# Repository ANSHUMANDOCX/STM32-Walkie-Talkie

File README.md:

# STM32 LoRa Walkie-Talkie

A custom walkie-talkie built on a bare STM32F411RET6 microcontroller and SX1278 LoRa radio module, designed from scratch in KiCad with a fully custom PCB.

---
## Inspiration
I made this STM32 Walkie Talkie to learn about STM32 since i have never worked with The ST chips and LoRa hence i though of it as a good opportunity for me to learn about these and make a good project out of it too. Also it gives me a chance to perfect wireless radio skills.
## Hardware 

| Component | Part | Purpose |
|---|---|---|
| MCU | STM32F411RET6 (LQFP-64) | Main processor |
| LoRa radio | Ra-02 (SX1278, 433 MHz) | Wireless communication |
| Mic amp | MAX9814 | Electret microphone amplifier with AGC |
| Speaker amp | MAX98357A | I2S class-D speaker amplifier |
| Display | Nokia 5110 (PCD8544) | Status display |
| LDO | MIC5219-3.3 | 3.3V regulation |
| Charger | TP4056 | Li-Ion battery charging |
| Protection | DW01A + AO3401A + FS8205 | Battery over/under voltage protection and Load sharing |
| Battery | 18650 Li-Ion (2500mAh) | Power source |

---

## Features

- Push-to-talk (PTT) voice transmission over LoRa
- Nokia 5110 display showing TX/RX status, RSSI, battery %, charging state
- LED indicators for TX and RX
- PWM buzzer with distinct tones for PTT, incoming call, low battery, charging complete etc
- Battery percentage via voltage divider on ADC
- Load sharing circuit — runs on USB power while charging battery
- TP4056 charging status readable by firmware
- SWD debug header for ST-Link V2 programming
- When USB is connected the system runs off USB directly and the battery charges independently. When USB is removed the load sharing circuit seamlessly switches to battery power.

---
Firmware us teseted and works fine
## Build 

Demo Links -
https://youtu.be/u5zcdfWUoc0?si=na0F3SUNMQuTFcsV
https://youtube.com/shorts/hGkoWbwqjJw?si=Fj_72HcpeDVytp3i
https://youtube.com/shorts/hm_hJY4Z-SY?si=CA80bZE5GAXgrqjr
https://youtu.be/_cB_pIMBPP0?si=Omx-B7MlO4rouQgG
https://youtu.be/SAzjPhdUsmI?si=3dBDZw_p-0JPJG1Q

## Schematic PCB and CAD

## BOM

| Product Name       | Part / Model         | Qty | Unit Price ($) | Total ($) | Vendor  | Link |
|-------------------|----------------------|-----|----------------|-----------|---------|------|
| 8MHz SMD Crystal  | X32258MOB4SI         | 2   | 0.08           | 0.15      | ROBU    | https://robu.in/product/x32258mob4si-yxc-crystal-oscillators-8mhz-surface-mount-crystal-12pf-%c2%b110ppm-%c2%b120ppm-smd3225-4p-crystals-rohs |
| STM32 MCU         | STM32F411RET6        | 2   | 2.88           | 5.76      | ROBU    | https://robu.in/product/stm32f411ret6-stmicroelectronics-3-6v-32-bit-risc-512kb-flash-arm-cortex-m4-mcu-dsp-fpu-art-accelerator-64-pin-lqfp |
| Push Button       | DS-316 SPST          | 2   | 0.12           | 0.24      | ROBU    | https://robu.in/product/ds-316-mini-push-button-switch-spst-2pinoff-on |
| IPEX to SMA Cable | RG178 15cm           | 2   | 1.60           | 3.20      | ROBU    | https://robu.in/product/15cm-ipex1-to-sma-female-connector-cable-11mm-rg178 |
| Mic Amplifier     | MAX9814ETDT          | 2   | 2.87           | 5.74      | ROBU    | https://robu.in/product/max9814etdt-analog-devices-microphone-amplifier-2-7-v-to-5-5-v-supply-1-ma-out-40-db-50db-60db-gain-tdfn-14 |
| Speaker AMP       | MAX98357A            | 2   | 2.37           | 4.73      | ROBU    | https://robu.in/product/1-month-warranty-560 |
| LoRa Module       | SX1278 RA-02         | 2   | 3.74           | 7.48      | ROBU    | https://robu.in/product/sx1278-lora-module-ra-02-433mhz-wireless-spread-spectrum-transmission |
| JST Connector     | 8-pin XH 2.54mm      | 2   | 0.77           | 1.55      | ROBU    | https://robu.in/product/8-pin-jst-xh-2-54mm-pitch-plug-and-socket-with-cable-3pcs |
| Speaker           | 8Ω Small Speaker     | 2   | 0.75           | 1.51      | Generic | https://sharvielectronics.com/product/speaker-8-ohm-trumpet-diameter-40mm-2-watt/ |
| Microphone        | Electret Mic Capsule | 2   | 0.11           | 0.22      | Generic | https://inkocean.in/products/microphones-9767-9-7-electret-microphone-a-microphone-with-pins-sensitivity-58 |
| Display           | Nokia 5110 LCD       | 2   | 3.01           | 6.02      | Generic | https://inkocean.in/products/nokia-5110-lcd-red-screen-blue-lcd-screen-module |
|HeatSet Insert Attatchment||1|6.2|6.2|Amazon|https://www.amazon.in/amiciTools-Heat-Insert-Soldering-Printing/dp/B0GFDZ5GL9/ref=asc_df_B0GFDZ5GL9?mcid=fe31e451fd45349b9016d36cd31d3876&hvadid=709875643605&hvpos=&hvnetw=g&hvrand=10961091970810594313&hvpone=&hvptwo=&hvqmt=&hvdev=c&hvdvcmdl=&hvlocint=&hvlocphy=1007828&hvtargid=pla-2466325763035&psc=1&hvocijid=10961091970810594313-B0GFDZ5GL9-&hvexpln=0|
| Passives          | SMD passives         | 1   | 5.38           | 5.38      | —       | — |
| PCB               | —                    | 1   | 3.00           | 3.00      | ALLPCB  | — |
| **TOTAL** |  |  |  | **44.98** |  |  |

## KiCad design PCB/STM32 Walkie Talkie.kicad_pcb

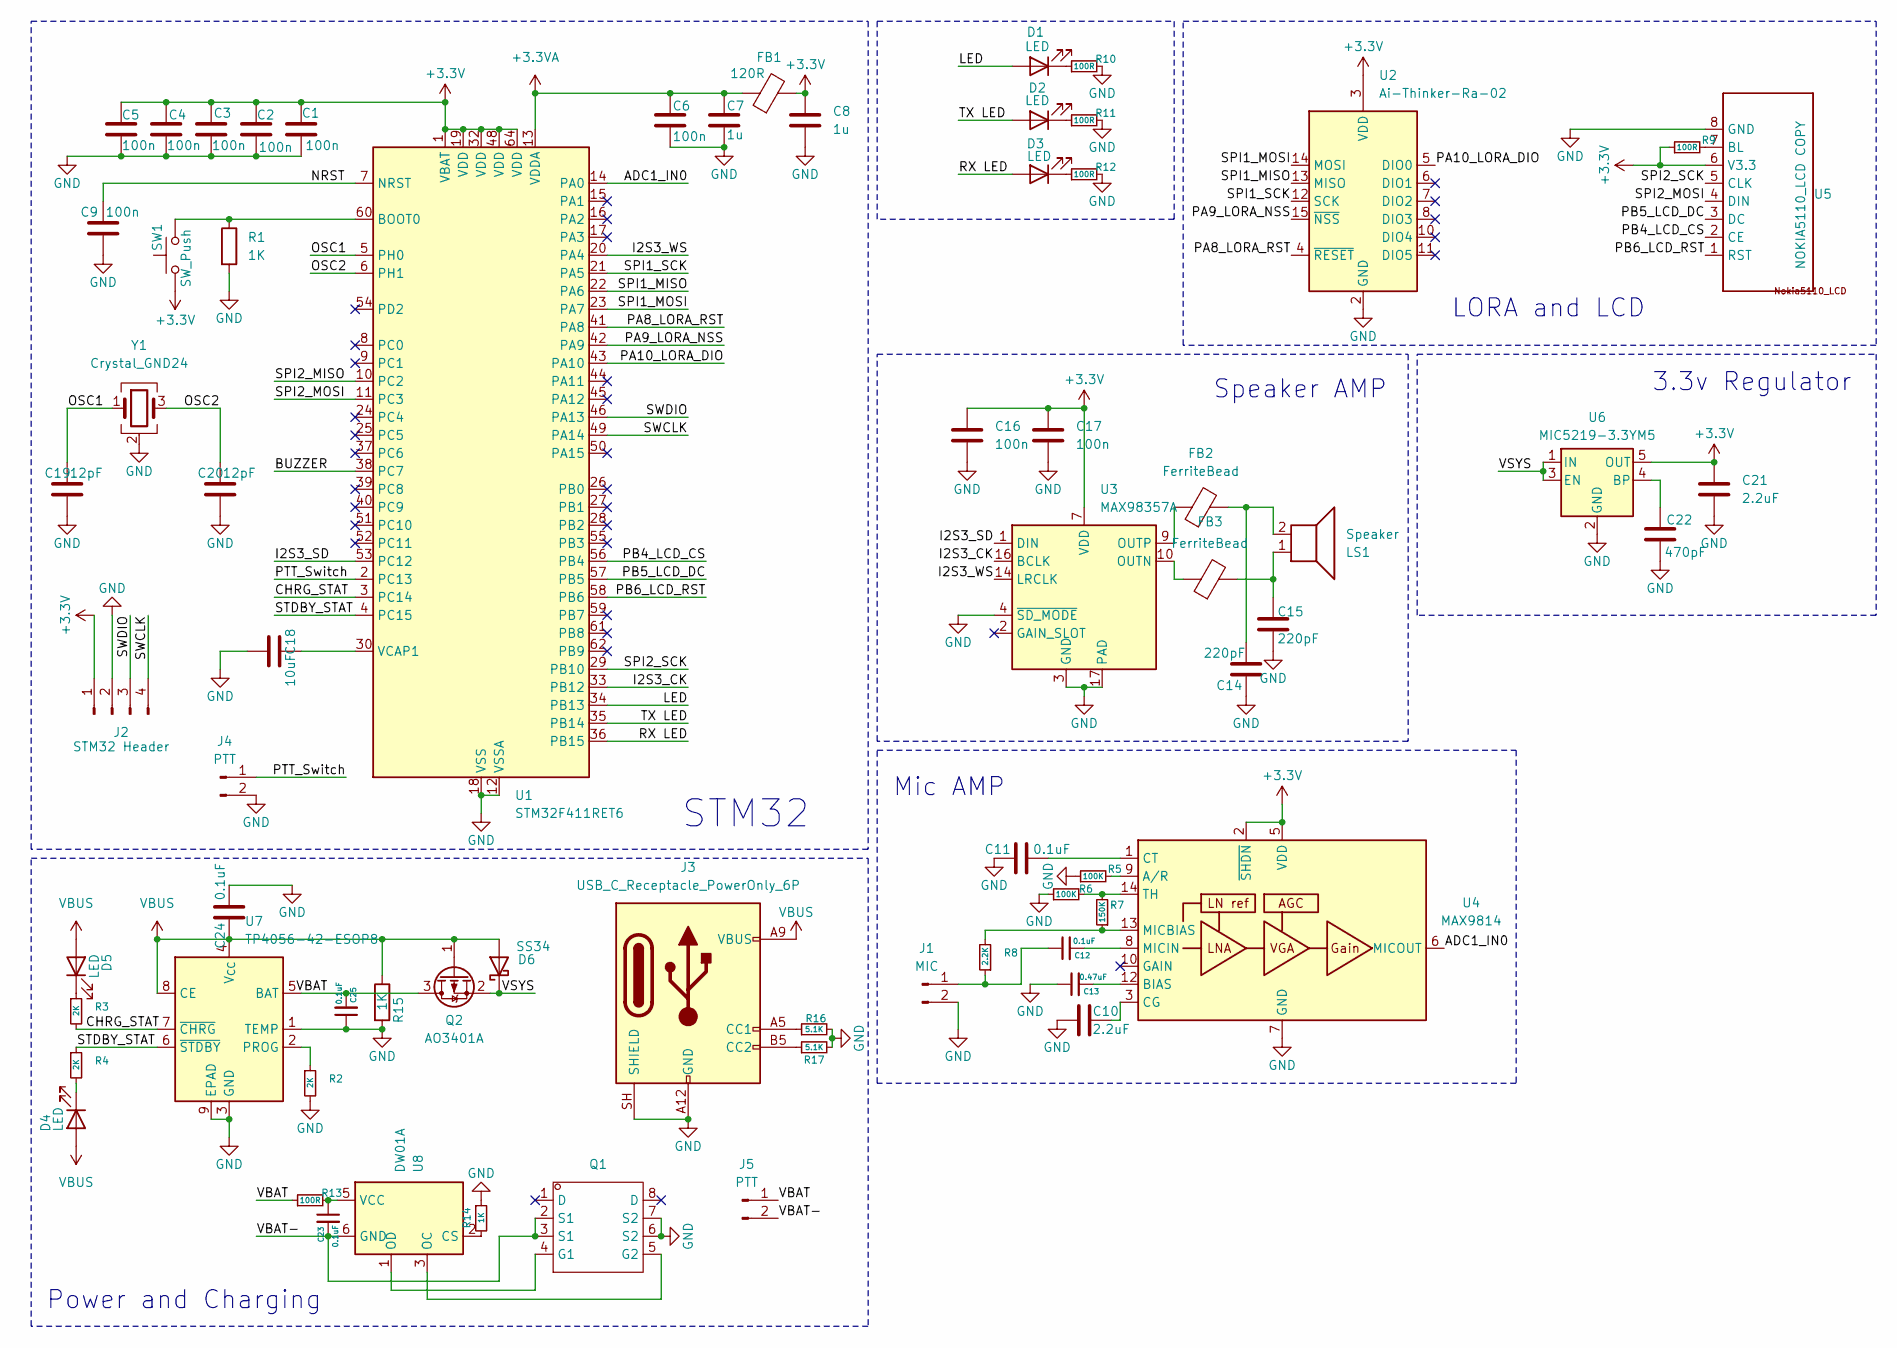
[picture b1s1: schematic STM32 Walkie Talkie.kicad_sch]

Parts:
C1, C2, C3, C4, C5, C6, C9, C16, C17: 100n; R_0603_1608Metric
C7, C8: 1u; R_0603_1608Metric
C10, C21: 2.2uF; C_0805_2012Metric
C11, C12, C23, C24, C25: 0.1uF; R_0603_1608Metric
C13: 0.47uF; R_0603_1608Metric
C14, C15: 220pF; R_0603_1608Metric
C18: 10uF; C_0805_2012Metric
C19, C20: 12pF; R_0603_1608Metric
C22: 470pF; R_0603_1608Metric
D1, D2, D3, D4, D5: LED; LED_0603_1608Metric
D6: SS34; D_SMA
FB1: 120R; R_0603_1608Metric
FB2, FB3: FerriteBead; R_0603_1608Metric
J1: MIC; JST_XH_B2B-XH-A_1x02_P2.50mm_Vertical
J2: STM32 Header; PinHeader_1x04_P2.54mm_Vertical
J3: USB_C_Receptacle_PowerOnly_6P; USB_C_Receptacle_GCT_USB4125-xx-x_6P_TopMnt_Horizontal
J4, J5: PTT; JST_XH_B2B-XH-A_1x02_P2.50mm_Vertical
LS1: Speaker; JST_XH_B2B-XH-A_1x02_P2.50mm_Vertical
Q1: TSSOP-8_L4.4-W3.0-P0.65-LS6.4-BL-2; Manufacturer Part FS8205A; LCSC Part Name 2个N沟道 耐压:20V 电流:6A
Q2: AO3401A; SOT-23
R1, R14, R15: 1K; R_0603_1608Metric
R2, R3, R4: 2K; R_0603_1608Metric
R5, R6: 100K; R_0603_1608Metric
R7: 150K; R_0603_1608Metric
R8: 2.2K; R_0603_1608Metric
R9, R10, R11, R12, R13: 100R; R_0603_1608Metric
R16, R17: 5.1K; R_0603_1608Metric
SW1: SW_Push; SW_SPST_TS-1088-xR025
U1: STM32F411RET6; LQFP-64_10x10mm_P0.5mm
U2: Ai-Thinker-Ra-02; Ai-Thinker-Ra-01-LoRa
U3: MAX98357A; TQFN-16-1EP_3x3mm_P0.5mm_EP1.23x1.23mm
U4: MAX9814; TDFN-14-1EP_3x3mm_P0.4mm_EP1.78x2.35mm
U5: NOKIA5110_LCD COPY; JST_XH_B8B-XH-A_1x08_P2.50mm_Vertical
U6: MIC5219-3.3YM5; SOT-23-5
U7: TP4056-42-ESOP8; SOIC-8-1EP_3.9x4.9mm_P1.27mm_EP2.41x3.3mm_ThermalVias
U8: DW01A; SOT-23-6
Y1: Crystal_GND24; Crystal_SMD_SeikoEpson_TSX3225-4Pin_3.2x2.5mm

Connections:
+3.3V: C1.1, C2.1, C3.1, C4.1, C5.1, C8.1, C16.1, C17.1, C21.1, FB1.2, J2.1, R9.1, SW1.1, U1.1 (VBAT), U1.19 (VDD), U1.32 (VDD), U1.48 (VDD), U1.64 (VDD), U2.3 (VDD), U3.7 (VDD), U3.8 (VDD), U4.2 (~SHDN), U4.5 (VDD), U5.6 (V3.3), U6.5 (OUT)
+3.3VA: C6.1, C7.1, FB1.1, U1.13 (VDDA)
/ADC1_IN0: U1.14 (PA0), U4.6 (MICOUT)
/BUZZER: U1.38 (PC7)
/CHRG_STAT: R3.2, U1.3 (PC14), U7.7 (~CHRG)
/I2S3_CK: U1.33 (PB12), U3.16 (BCLK)
/I2S3_SD: U1.53 (PC12), U3.1 (DIN)
/I2S3_WS: U1.20 (PA4), U3.14 (LRCLK)
/LED: D1.2 (A), U1.34 (PB13)
/NRST: C9.1, U1.7 (NRST)
/OSC1: C19.1, U1.5 (PH0), Y1.1
/OSC2: C20.1, U1.6 (PH1), Y1.3
/PA8_LORA_RST: U1.41 (PA8), U2.4 (~RESET)
/PA9_LORA_NSS: U1.42 (PA9), U2.15 (~NSS)
/PA10_LORA_DIO: U1.43 (PA10), U2.5 (DIO0)
/PB4_LCD_CS: U1.56 (PB4), U5.2 (CE)
/PB5_LCD_DC: U1.57 (PB5), U5.3 (DC)
/PB6_LCD_RST: U1.58 (PB6), U5.1 (RST)
/PTT_Switch: J4.1, U1.2 (PC13)
/RX LED: D3.2 (A), U1.36 (PB15)
/SPI1_MISO: U1.22 (PA6), U2.13 (MISO)
/SPI1_MOSI: U1.23 (PA7), U2.14 (MOSI)
/SPI1_SCK: U1.21 (PA5), U2.12 (SCK)
/SPI2_MISO: U1.10 (PC2)
/SPI2_MOSI: U1.11 (PC3), U5.4 (DIN)
/SPI2_SCK: U1.29 (PB10), U5.5 (CLK)
/STDBY_STAT: R4.1, U1.4 (PC15), U7.6 (~STDBY)
/SWCLK: J2.4, U1.49 (PA14)
/SWDIO: J2.3, U1.46 (PA13)
/TX LED: D2.2 (A), U1.35 (PB14)
/VBAT: C25.2, J5.1, Q2.3 (D), R13.1, U7.5 (BAT)
/VBAT-: C23.2, J5.2, Q1.2 (S1), Q1.3 (S1), U8.6 (GND)
/VSYS: D6.1 (K), Q2.2 (S), U6.1 (IN), U6.3 (EN)
GND: C1.2, C2.2, C3.2, C4.2, C5.2, C6.2, C7.2, C8.2, C9.2, C10.1, C11.1, C13.1, C14.2, C15.2, C16.2, C17.2, C18.2, C19.2, C20.2, C21.2, C22.2, C24.2, C25.1, J1.2, J2.2, J3.A12 (GND), J3.B12 (GND), J3.SH (SHIELD), J4.2, Q1.6 (S2), Q1.7 (S2), R1.2, R2.2, R5.1, R6.1, R10.2, R11.2, R12.2, R14.1, R15.2, R16.2, R17.2, U1.12 (VSSA), U1.18 (VSS), U1.31 (VSS), U1.47 (VSS), U1.63 (VSS), U2.1 (GND), U2.2 (GND), U2.9 (GND), U2.16 (GND), U3.3 (GND), U3.4 (~SD_MODE), U3.11 (GND), U3.15 (GND), U3.17 (PAD), U4.4 (GND), U4.7 (GND), U4.11 (GND), U4.15 (GND), U5.8 (GND), U6.2 (GND), U7.1 (TEMP), U7.3 (GND), U7.9 (EPAD), U8.4 (TD), Y1.2 (G), Y1.4 (G)
unnamed: C14.1, FB2.2, LS1.2
unnamed: C15.1, FB3.2, LS1.1
unnamed: D1.1 (K), R10.1
unnamed: D2.1 (K), R11.1
unnamed: D3.1 (K), R12.1
unnamed: D4.1 (K), R4.2
unnamed: D5.1 (K), R3.1
unnamed: C12.1, J1.1, R8.1
unnamed: J3.A5 (CC1), R16.1
unnamed: J3.B5 (CC2), R17.1
unnamed: Q1.4 (G1), U8.1 (OD)
unnamed: Q1.5 (G2), U8.3 (OC)
unnamed: R1.1, SW1.2, U1.60 (BOOT0)
unnamed: C18.1, U1.30 (VCAP1)
unnamed: FB3.1, U3.10 (OUTN)
unnamed: FB2.1, U3.9 (OUTP)
unnamed: R5.2, U4.9 (A/R)
unnamed: C13.2, U4.12 (BIAS)
unnamed: C10.2, U4.3 (CG)
unnamed: C11.2, U4.1 (CT)
unnamed: R7.1, R8.2, U4.13 (MICBIAS)
unnamed: C12.2, U4.8 (MICIN)
unnamed: R6.2, R7.2, U4.14 (TH)
unnamed: R9.2, U5.7 (BL)
unnamed: C22.1, U6.4 (BP)
unnamed: R2.1, U7.2 (PROG)
unnamed: R14.2, U8.2 (CS)
unnamed: C23.1, R13.2, U8.5 (VCC)
VBUS: C24.1, D4.2 (A), D5.2 (A), D6.2 (A), J3.A9 (VBUS), J3.B9 (VBUS), Q2.1 (G), R15.1, U7.4 (V_{CC}), U7.8 (CE)

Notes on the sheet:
3.3v Regulator
Mic AMP
Speaker AMP
Power and Charging
LORA and LCD
STM32

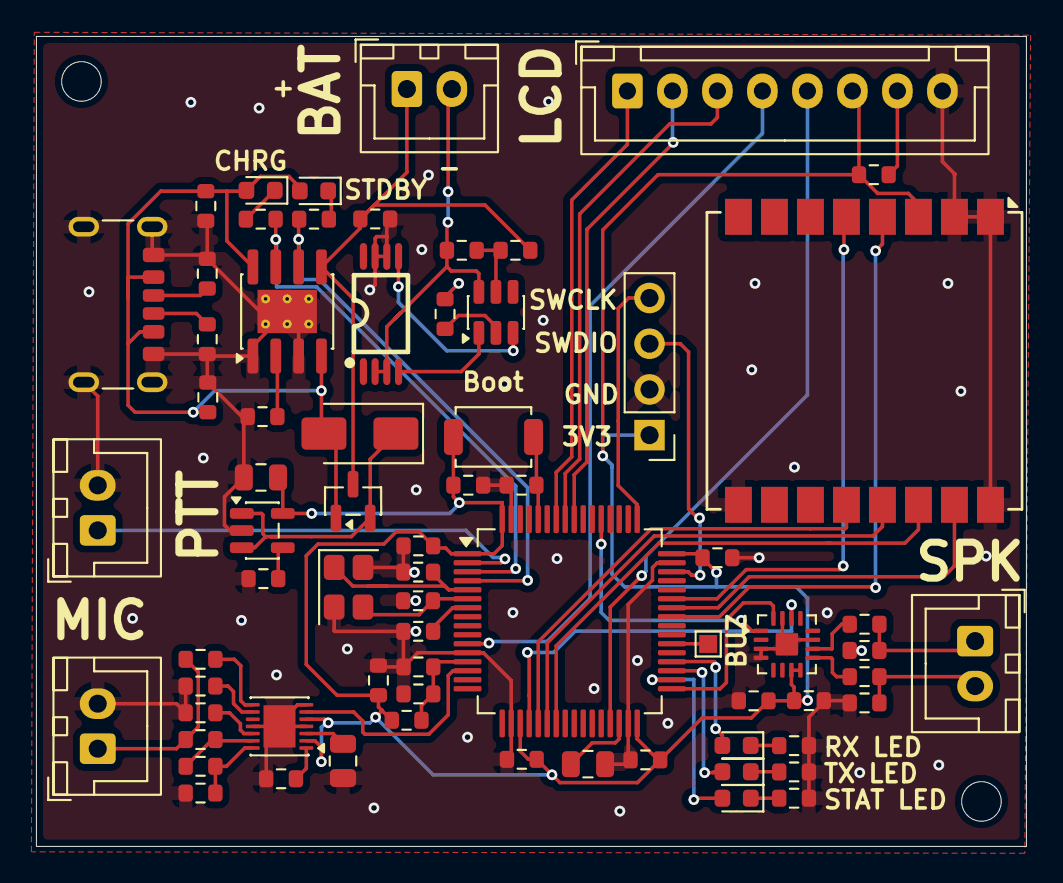
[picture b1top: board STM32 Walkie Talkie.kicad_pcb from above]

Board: 2 copper layers, 55.0 x 45.0 mm, 69 parts (0 on the bottom side), 61 nets.

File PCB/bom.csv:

Designator,Footprint,Quantity,Value,LCSC Part #
"C1, C16, C17, C2, C3, C4, C5, C6, C9",0603,9,100n,
"C10, C21",0805,2,2.2uF,
"C11, C12, C23, C24, C25",0603,5,0.1uF,
C13,0603,1,0.47uF,
"C14, C15",0603,2,220pF,
C18,0805,1,10uF,
"C19, C20",0603,2,12pF,
C22,0603,1,470pF,
"C7, C8",0603,2,1u,
"D1, D2, D3, D4, D5",0603,5,LED,
D6,D_SMA,1,SS34,
FB1,0603,1,120R,
"FB2, FB3",0603,2,FerriteBead,
J1,JST_XH_B2B-XH-A_1x02_P2.50mm_Vertical,1,MIC,
J2,PinHeader_1x04_P2.54mm_Vertical,1,STM32 Header,
J3,USB_C_Receptacle_GCT_USB4125-xx-x_6P_TopMnt_Horizontal,1,USB_C_Receptacle_PowerOnly_6P,
"J4, J5",JST_XH_B2B-XH-A_1x02_P2.50mm_Vertical,2,PTT,
LS1,JST_XH_B2B-XH-A_1x02_P2.50mm_Vertical,1,Speaker,
Q1,TSSOP-8_L4.4-W3.0-P0.65-LS6.4-BL-2,1,~,
Q2,SOT-23,1,AO3401A,
"R1, R14, R15",0603,3,1K,
"R10, R11, R12, R13, R9",0603,5,100R,
"R16, R17",0603,2,5.1K,
"R2, R3, R4",0603,3,2K,
"R5, R6",0603,2,100K,
R7,0603,1,150K,
R8,0603,1,2.2K,
SW1,SW_SPST_TS-1088-xR025,1,SW_Push,
U1,LQFP-64_10x10mm_P0.5mm,1,STM32F411RET6,
U2,Ai-Thinker-Ra-01-LoRa,1,Ai-Thinker-Ra-02,
U3,TQFN-16-1EP_3x3mm_P0.5mm_EP1.23x1.23mm,1,MAX98357A,
U4,TDFN-14-1EP_3x3mm_P0.4mm_EP1.78x2.35mm,1,MAX9814,
U5,JST_XH_B8B-XH-A_1x08_P2.50mm_Vertical,1,NOKIA5110_LCD COPY,
U6,SOT-23-5,1,MIC5219-3.3YM5,
U7,SOIC-8-1EP_3.9x4.9mm_P1.27mm_EP2.41x3.3mm_ThermalVias,1,TP4056-42-ESOP8,
U8,SOT-23-6,1,DW01A,
Y1,Crystal_SMD_SeikoEpson_TSX3225-4Pin_3.2x2.5mm,1,Crystal_GND24,

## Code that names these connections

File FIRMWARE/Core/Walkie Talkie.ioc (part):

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Mcu.Name=STM32F411R(C-E)Tx
Mcu.Package=LQFP64
Mcu.UserName=STM32F411RETx
PA0-WKUP.Signal=ADCx_IN0
PA10.GPIOParameters=GPIO_Label
PA10.GPIO_Label=LORA_DIO
PA10.Signal=GPXTI10
PA13.Mode=Serial_Wire
PA13.Signal=SYS_JTMS-SWDIO
PA14.Mode=Serial_Wire
PA14.Signal=SYS_JTCK-SWCLK
PA15.Mode=Half_Duplex_Master
PA15.Signal=I2S3_WS
PA5.GPIOParameters=GPIO_Label
PA5.GPIO_Label=LORA_SCK
PA5.Mode=Full_Duplex_Master
PA5.Signal=SPI1_SCK
PA6.GPIOParameters=GPIO_Label
PA6.GPIO_Label=LORA_MISO
PA6.Mode=Full_Duplex_Master
PA6.Signal=SPI1_MISO
PA7.GPIOParameters=GPIO_Label
PA7.GPIO_Label=LORA_MOSI
PA7.Mode=Full_Duplex_Master
PA7.Signal=SPI1_MOSI
PA8.GPIOParameters=GPIO_Label
PA8.GPIO_Label=LORA_RST
PA8.Signal=GPIO_Output
PA9.GPIOParameters=GPIO_Label
PA9.GPIO_Label=LORA_NSS
PA9.Signal=GPIO_Output
PB10.GPIOParameters=GPIO_Label
PB10.GPIO_Label=LCD_SCK
PB10.Mode=Full_Duplex_Master
PB10.Signal=SPI2_SCK
PB12.Mode=Half_Duplex_Master
PB12.Signal=I2S3_CK
PB13.GPIOParameters=GPIO_Label
PB13.GPIO_Label=LED_Debug
PB13.Signal=GPIO_Output
PB14.GPIOParameters=GPIO_Label
PB14.GPIO_Label=TX_LED
PB14.Signal=GPIO_Output
PB15.GPIOParameters=GPIO_Label
PB15.GPIO_Label=RX_LED
PB15.Signal=GPIO_Output
PB4.GPIOParameters=GPIO_Label
PB4.GPIO_Label=LCD_CS
PB4.Signal=GPIO_Output
PB5.GPIOParameters=GPIO_Label
PB5.GPIO_Label=LCD_DC
PB5.Signal=GPIO_Output
PB6.GPIOParameters=GPIO_Label
PB6.GPIO_Label=LCD_RST
PB6.Signal=GPIO_Output
PC12.Mode=Half_Duplex_Master
PC12.Signal=I2S3_SD
PC14-OSC32_IN.GPIOParameters=GPIO_Label
PC14-OSC32_IN.GPIO_Label=CHAR_STAT
PC14-OSC32_IN.Signal=GPIO_Input
PC15-OSC32_OUT.GPIOParameters=GPIO_PuPd,GPIO_Label
PC15-OSC32_OUT.GPIO_Label=STDBY_STAT
PC15-OSC32_OUT.GPIO_PuPd=GPIO_PULLUP
PC15-OSC32_OUT.Signal=GPIO_Input
PC2.Mode=Full_Duplex_Master
PC2.Signal=SPI2_MISO
PC3.Mode=Full_Duplex_Master
PC3.Signal=SPI2_MOSI
PC4.GPIOParameters=GPIO_PuPd,GPIO_Label,GPIO_ModeDefaultEXTI
PC4.GPIO_Label=PTT_Switch
PC4.GPIO_ModeDefaultEXTI=GPIO_MODE_IT_RISING_FALLING
PC4.GPIO_PuPd=GPIO_PULLUP
PC4.Signal=GPXTI4
PC5.GPIOParameters=GPIO_Label
PC5.GPIO_Label=Voltage_divider
PC5.Signal=ADCx_IN15
PC7.GPIOParameters=GPIO_Label
PC7.GPIO_Label=Buzzer
PC7.Signal=S_TIM3_CH2
PH0\ -\ OSC_IN.Mode=HSE-External-Oscillator
PH0\ -\ OSC_IN.Signal=RCC_OSC_IN
PH1\ -\ OSC_OUT.Mode=HSE-External-Oscillator
PH1\ -\ OSC_OUT.Signal=RCC_OSC_OUT
RCC.HSE_VALUE=8000000
RCC.SYSCLKFreq_VALUE=16000000
board=custom

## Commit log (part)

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2026-06-27 Document progress of STM32 Walkie Talkie build
    Added detailed journal entries documenting the progress and challenges faced while building the STM32 Walkie Talkie project, including assembly, troubleshooting, and testing phases.
